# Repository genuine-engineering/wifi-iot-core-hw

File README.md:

# WIFI-IOT-CORE for IoT production project

_Wifi IoT Core_ project is to combine STM32 + ESP8266.

- ESP8266 is an amazing but cheap wifi chip. However it has many limitions, such as: no USB, limited analog interface, few I/O etc, while applications which are developed on it often need USB-Serial communication. Therefore many ESP8266-based modules in the world are added USB-TTL chip. While this brings some value to developing work, the value is just little in practical use. The design in this _Wifi IoT Core_ project uses the cheap STM32, with USB interface, to ease development, and complements many other features which are missing in ESP8266.

- The _Wifi IoT Core_ project including:

    + [wifi-iot-core-hw](https://github.com/genuine-engineering/wifi-iot-core-hw). Hardware is designed with [KiCad](http://kicad-pcb.org/)
    + [wifi-iot-core-stm32-fw](https://github.com/genuine-engineering/wifi-iot-core-stm32-fw). Firmware for STM32, based on [libopencm3](https://github.com/libopencm3/libopencm3)
    + [wifi-iot-core-esp8266-fw](https://github.com/genuine-engineering/wifi-iot-core-esp8266-fw). Firmware for ESP8266, based on [Espressif SDK 2.0](https://espressif.com/en/support/download/sdks-demos)

# Wifi-iot-core-hw
## Overview
The hardware is designed with [KiCad](http://kicad-pcb.org/) software. It includes two main components: ESP8266 and STM32F103C8T6.

 - STM32 has USB interface and is connected with ESP8266 via UART.

 - The output pins of the STM32 and ESP8266 are exposed for external use.

## Schematic

## PCB

## 3D

## BOM

| Refs                      | Value           | Footprint                            |
|---------------------------|-----------------|--------------------------------------|
| C7                        | 15pf            | lib:C_0603                           |
| C1,C9-C12,C15,C17,C19,C20 | 0.1uF           | lib:C_0603                           |
| C4,C5                     | 10pF            | lib:C_0603                           |
| C6                        | 15pF            | lib:C_0603                           |
| C16,C18                   | 1uF             | lib:C_0603                           |
| C3                        | 100nF           | lib:C_0603                           |
| C21                       | 10nF            | lib:C_0603                           |
| C2,C13,C14                | 10uF-50v        | Capacitors_SMD:C_1210                |
| C8                        | 470pF           | lib:C_0603                           |
| R11,R12                   | 22              | lib:R_0603                           |
| R10                       | 1.5K            | lib:R_0603                           |
| R2-R5                     | 10K             | lib:R_0603                           |
| R9                        | 0R              | lib:R_0603                           |
| R1,R6-R8,R13              | 10k             | lib:R_0603                           |
| SW1                       | RST             | lib:SW_SPST_B3U-1000P-B              |
| SW2                       | SW_PUSH_SMALL_H | lib:SW_SPST_B3U-1000P-B              |
| U1                        | ESP-07v2        | lib:ESP-07v2-smd-16pin               |
| U2                        | STM32F103C8Tx   | lib:LQFP-48_Pin1.7x0.3mm_Pitch0.5mm  |
| U3                        | LP2985LV        | TO_SOT_Packages_SMD:SOT-23-5         |
| P1,P2                     | CONN_01X20      | Pin_Headers:Pin_Header_Straight_1x20 |
| P7                        | CONN_01X04      | Pin_Headers:Pin_Header_Straight_1x04 |
| P3-P6                     | CONN_01X01      | lib:MountingHole_2mm                 |
| P8                        | USB             | lib:Micro_usb_B_smd                  |
| Y2                        | 32.687          | lib:crystal_smd_32.768_2Pin          |
| Y1                        | 8MHz            | lib:Crystal_SMD_5032_4Pads           |
| D2                        | Led             | LEDs:LED_0805                        |
| D1                        | Led GPIO16      | LEDs:LED_0805                        |

## Gerber file

[Wifi IOT Core HW Gerber file](assets/gerber.zip)

## CC-BY license

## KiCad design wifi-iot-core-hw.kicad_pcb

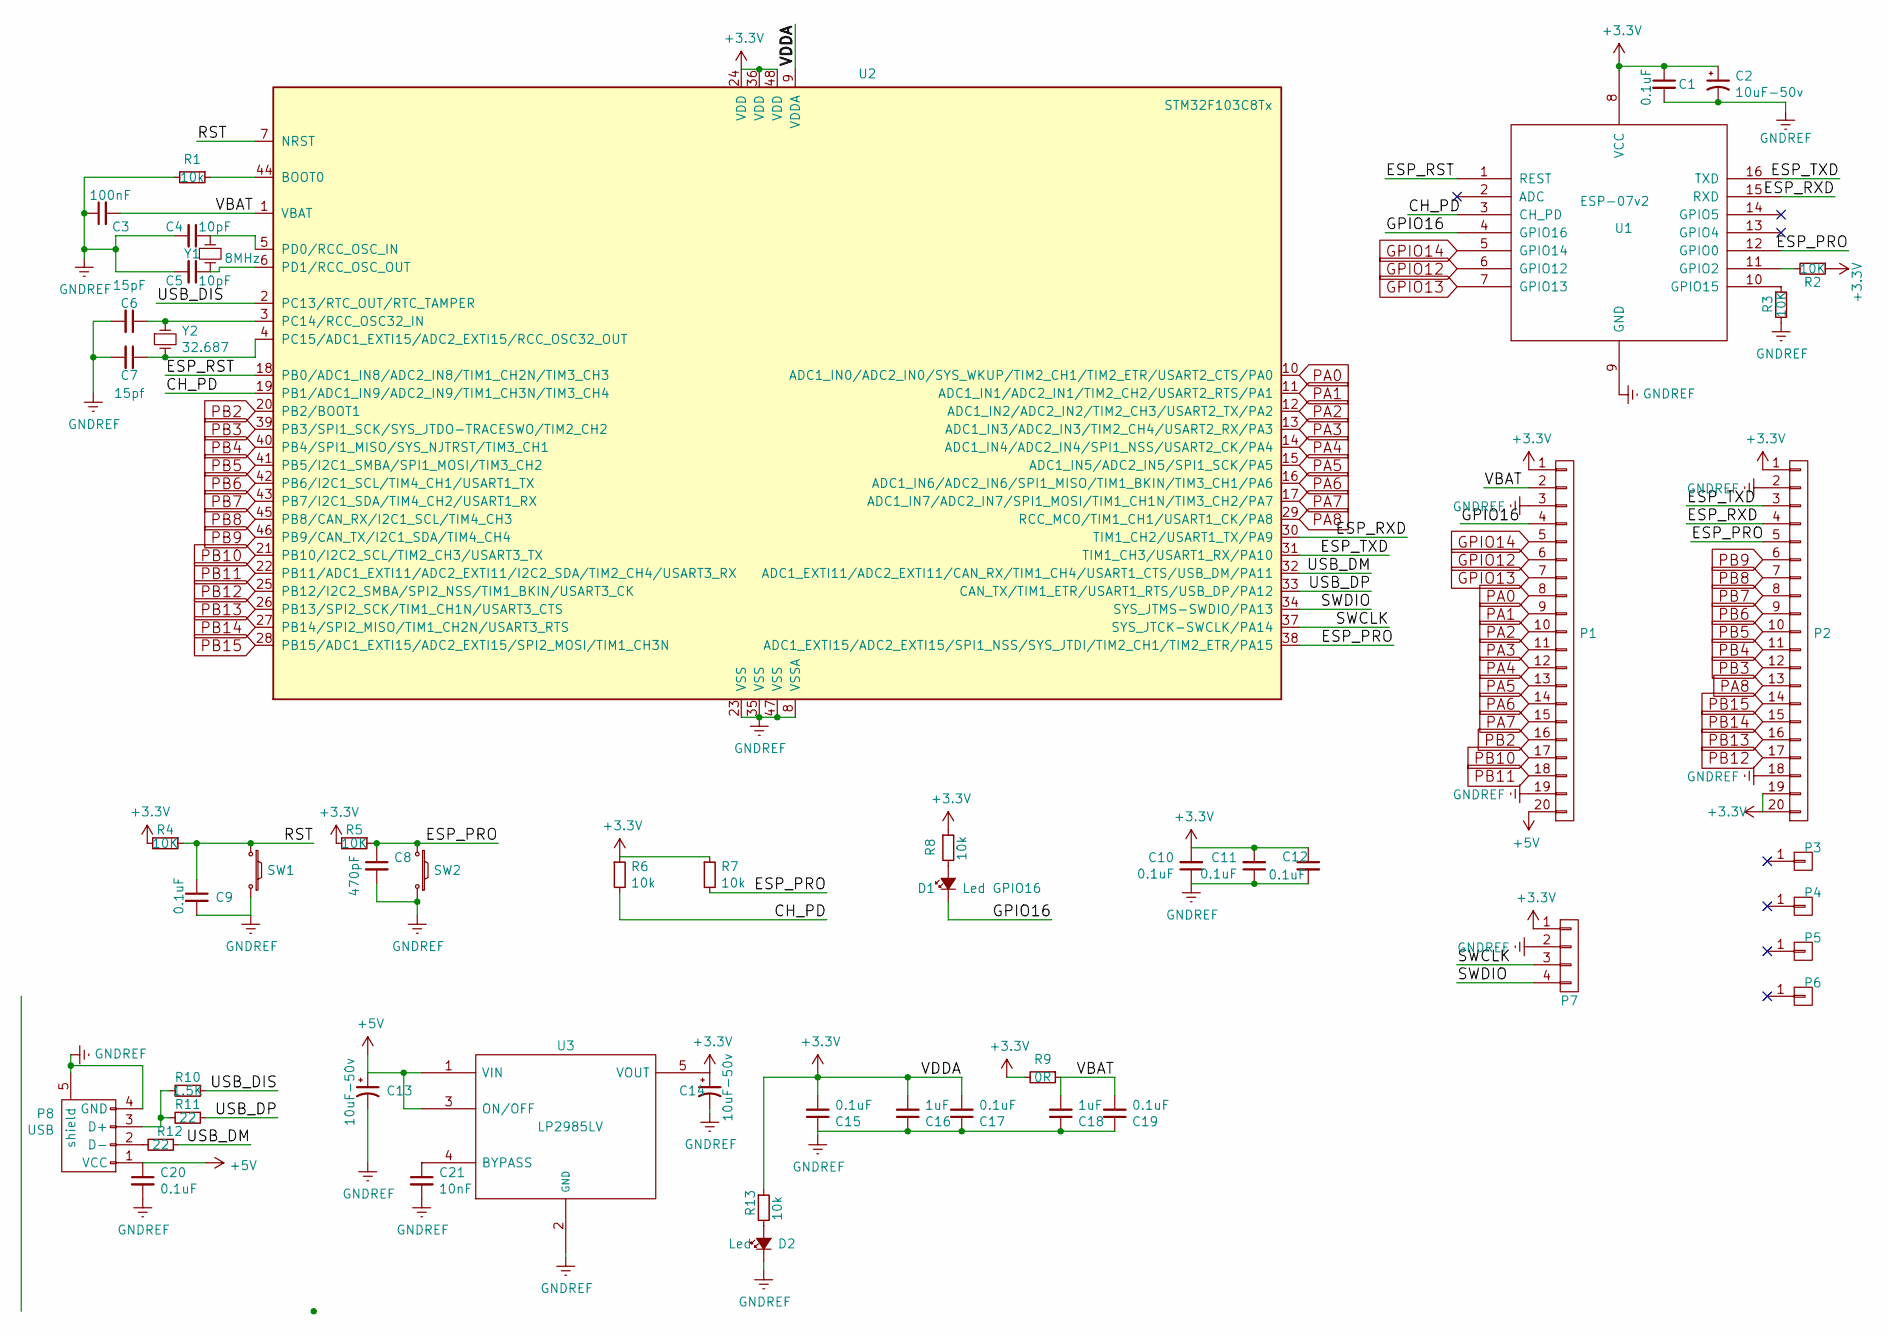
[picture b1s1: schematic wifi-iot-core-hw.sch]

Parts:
C1, C9, C10, C11, C12, C15, C17, C19, C20: 0.1uF; C_0603
C2, C13, C14: 10uF-50v; C_1210
C3: 100nF; C_0603
C4, C5: 10pF; C_0603
C6: 15pF; C_0603
C7: 15pf; C_0603
C8: 470pF; C_0603
C16, C18: 1uF; C_0603
C21: 10nF; C_0603
D1: Led GPIO16; LED_0805
D2: Led; LED_0805
P1, P2: CONN_01X20; Pin_Header_Straight_1x20
P3, P4, P5, P6: CONN_01X01; MountingHole_2mm
P7: CONN_01X04; Pin_Header_Straight_1x04
P8: USB; Micro_usb_B_smd
R1, R6, R7, R8, R13: 10k; R_0603
R2, R3, R4, R5: 10K; R_0603
R9: 0R; R_0603
R10: 1.5K; R_0603
R11, R12: 22; R_0603
SW1: RST; SW_SPST_B3U-1000P-B
SW2: SW_PUSH_SMALL_H; SW_SPST_B3U-1000P-B
U1: ESP-07v2; ESP-07v2-smd-16pin
U2: STM32F103C8Tx; LQFP-48_Pin1.7x0.3mm_Pitch0.5mm
U3: LP2985LV; SOT-23-5
Y1: 8MHz; Crystal_SMD_5032_4Pads
Y2: 32.687; crystal_smd_32.768_2Pin

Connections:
+3V3: C1.1, C2.1, C10.2, C11.2, C12.1, C14.1, C15.2, C16.2, C17.2, P1.1, P2.1, P2.19, P2.20, P7.1, R2.1, R4.2, R5.2, R6.1, R7.1, R8.1, R9.2, R13.1, U1.8 (VCC), U2.9 (VDDA), U2.24 (VDD), U2.36 (VDD), U2.48 (VDD), U3.5 (VOUT)
+5V: C13.1, C20.1, P1.20, P8.1 (VCC), U3.1 (VIN), U3.3 (ON/OFF)
/CH_PD: R6.2, U1.3 (CH_PD), U2.19 (PB1/ADC1_IN9/ADC2_IN9/TIM1_CH3N/TIM3_CH4)
/ESP_PRO: C8.1, P2.5, R5.1, R7.2, SW2.1, U1.12 (GPIO0), U2.38 (ADC1_EXTI15/ADC2_EXTI15/SPI1_NSS/SYS_JT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)
/ESP_RST: U1.1 (REST), U2.18 (PB0/ADC1_IN8/ADC2_IN8/TIM1_CH2N/TIM3_CH3)
/ESP_RXD: P2.4, U1.15 (RXD), U2.30 (TIM1_CH2/USART1_TX/PA9)
/ESP_TXD: P2.3, U1.16 (TXD), U2.31 (TIM1_CH3/USART1_RX/PA10)
/GPIO16: D1.1 (K), P1.4, U1.4 (GPIO16)
/RST: C9.1, R4.1, SW1.1, U2.7 (NRST)
/SWCLK: P7.3, U2.37 (SYS_JTCK-SWCLK/PA14)
/SWDIO: P7.4, U2.34 (SYS_JTMS-SWDIO/PA13)
/USB_DIS: R10.1, U2.2 (PC13/RTC_OUT/RTC_TAMPER)
/USB_DM: R12.1, U2.32 (ADC1_EXTI11/ADC2_EXTI11/CAN_RX/TIM1_CH4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)
/USB_DP: R11.1, U2.33 (CAN_TX/TIM1_ETR/USART1_RTS/USB_DP/PA12)
/VBAT: C3.2, C18.2, C19.2, P1.2, R9.1, U2.1 (VBAT)
GNDREF: C1.2, C2.2, C3.1, C4.2, C5.2, C6.2, C7.2, C8.2, C9.2, C10.1, C11.1, C12.2, C13.2, C14.2, C15.1, C16.1, C17.1, C18.1, C19.1, C20.2, C21.2, D2.1 (K), P1.3, P1.19, P2.2, P2.18, P7.2, P8.4 (GND), P8.5 (shield), R1.2, R3.2, SW1.2, SW2.2, U1.9 (GND), U2.8 (VSSA), U2.23 (VSS), U2.35 (VSS), U2.47 (VSS), U3.2 (GND)
GPIO12: P1.6, U1.6 (GPIO12)
GPIO13: P1.7, U1.7 (GPIO13)
GPIO14: P1.5, U1.5 (GPIO14)
unnamed: C4.1, U2.5 (PD0/RCC_OSC_IN), Y1.1
unnamed: C5.1, U2.6 (PD1/RCC_OSC_OUT), Y1.2
unnamed: C6.1, U2.3 (PC14/RCC_OSC32_IN), Y2.1
unnamed: C7.1, U2.4 (PC15/ADC1_EXTI15/ADC2_EXTI15/RCC_OSC32_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), Y2.2
unnamed: C21.1, U3.4 (BYPASS)
unnamed: D1.2 (A), R8.2
unnamed: D2.2 (A), R13.2
unnamed: P8.2 (D-), R12.2
unnamed: P8.3 (D+), R10.2, R11.2
unnamed: R1.1, U2.44 (BOOT0)
unnamed: R2.2, U1.11 (GPIO2)
unnamed: R3.1, U1.10 (GPIO15)
PA0: P1.8, U2.10 (ADC1_IN0/ADC2_IN0/SYS_WKUP/TIM2_CH1/TIM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)
PA1: P1.9, U2.11 (ADC1_IN1/ADC2_IN1/TIM2_CH2/USART2_RTS/P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)
PA2: P1.10, U2.12 (ADC1_IN2/ADC2_IN2/TIM2_CH3/USART2_TX/PA2)
PA3: P1.11, U2.13 (ADC1_IN3/ADC2_IN3/TIM2_CH4/USART2_RX/PA3)
PA4: P1.12, U2.14 (ADC1_IN4/ADC2_IN4/SPI1_NSS/USART2_CK/PA4)
PA5: P1.13, U2.15 (ADC1_IN5/ADC2_IN5/SPI1_SCK/PA5)
PA6: P1.14, U2.16 (ADC1_IN6/ADC2_IN6/SPI1_MISO/TIM1_BKIN/T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)
PA7: P1.15, U2.17 (ADC1_IN7/ADC2_IN7/SPI1_MOSI/TIM1_CH1N/T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)
PA8: P2.13, U2.29 (RCC_MCO/TIM1_CH1/USART1_CK/PA8)
PB2: P1.16, U2.20 (PB2/BOOT1)
PB3: P2.12, U2.39 (PB3/SPI1_SCK/SYS_JTDO-TRACESWO/TIM2_CH2)
PB4: P2.11, U2.40 (PB4/SPI1_MISO/SYS_NJTRST/TIM3_CH1)
PB5: P2.10, U2.41 (PB5/I2C1_SMBA/SPI1_MOSI/TIM3_CH2)
PB6: P2.9, U2.42 (PB6/I2C1_SCL/TIM4_CH1/USART1_TX)
PB7: P2.8, U2.43 (PB7/I2C1_SDA/TIM4_CH2/USART1_RX)
PB8: P2.7, U2.45 (PB8/CAN_RX/I2C1_SCL/TIM4_CH3)
PB9: P2.6, U2.46 (PB9/CAN_TX/I2C1_SDA/TIM4_CH4)
PB10: P1.17, U2.21 (PB10/I2C2_SCL/TIM2_CH3/USART3_TX)
PB11: P1.18, U2.22 (PB11/ADC1_EXTI11/ADC2_EXTI11/I2C2_SDA/T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)
PB12: P2.17, U2.25 (PB12/I2C2_SMBA/SPI2_NSS/TIM1_BKIN/USART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)
PB13: P2.16, U2.26 (PB13/SPI2_SCK/TIM1_CH1N/USART3_CTS)
PB14: P2.15, U2.27 (PB14/SPI2_MISO/TIM1_CH2N/USART3_RTS)
PB15: P2.14, U2.28 (PB15/ADC1_EXTI15/ADC2_EXTI15/SPI2_MOSI/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)

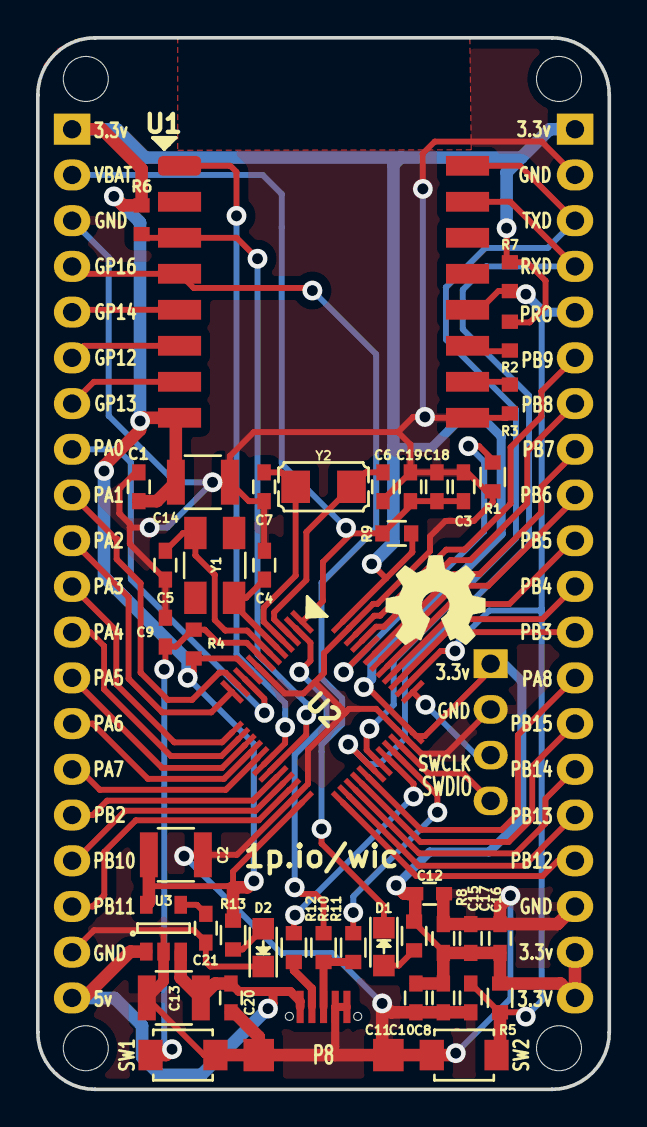
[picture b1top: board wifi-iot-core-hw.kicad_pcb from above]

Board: 2 copper layers, 31.8 x 58.4 mm, 52 parts (0 on the bottom side), 54 nets.

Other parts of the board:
VAL**: oshw_logo_500; logo5

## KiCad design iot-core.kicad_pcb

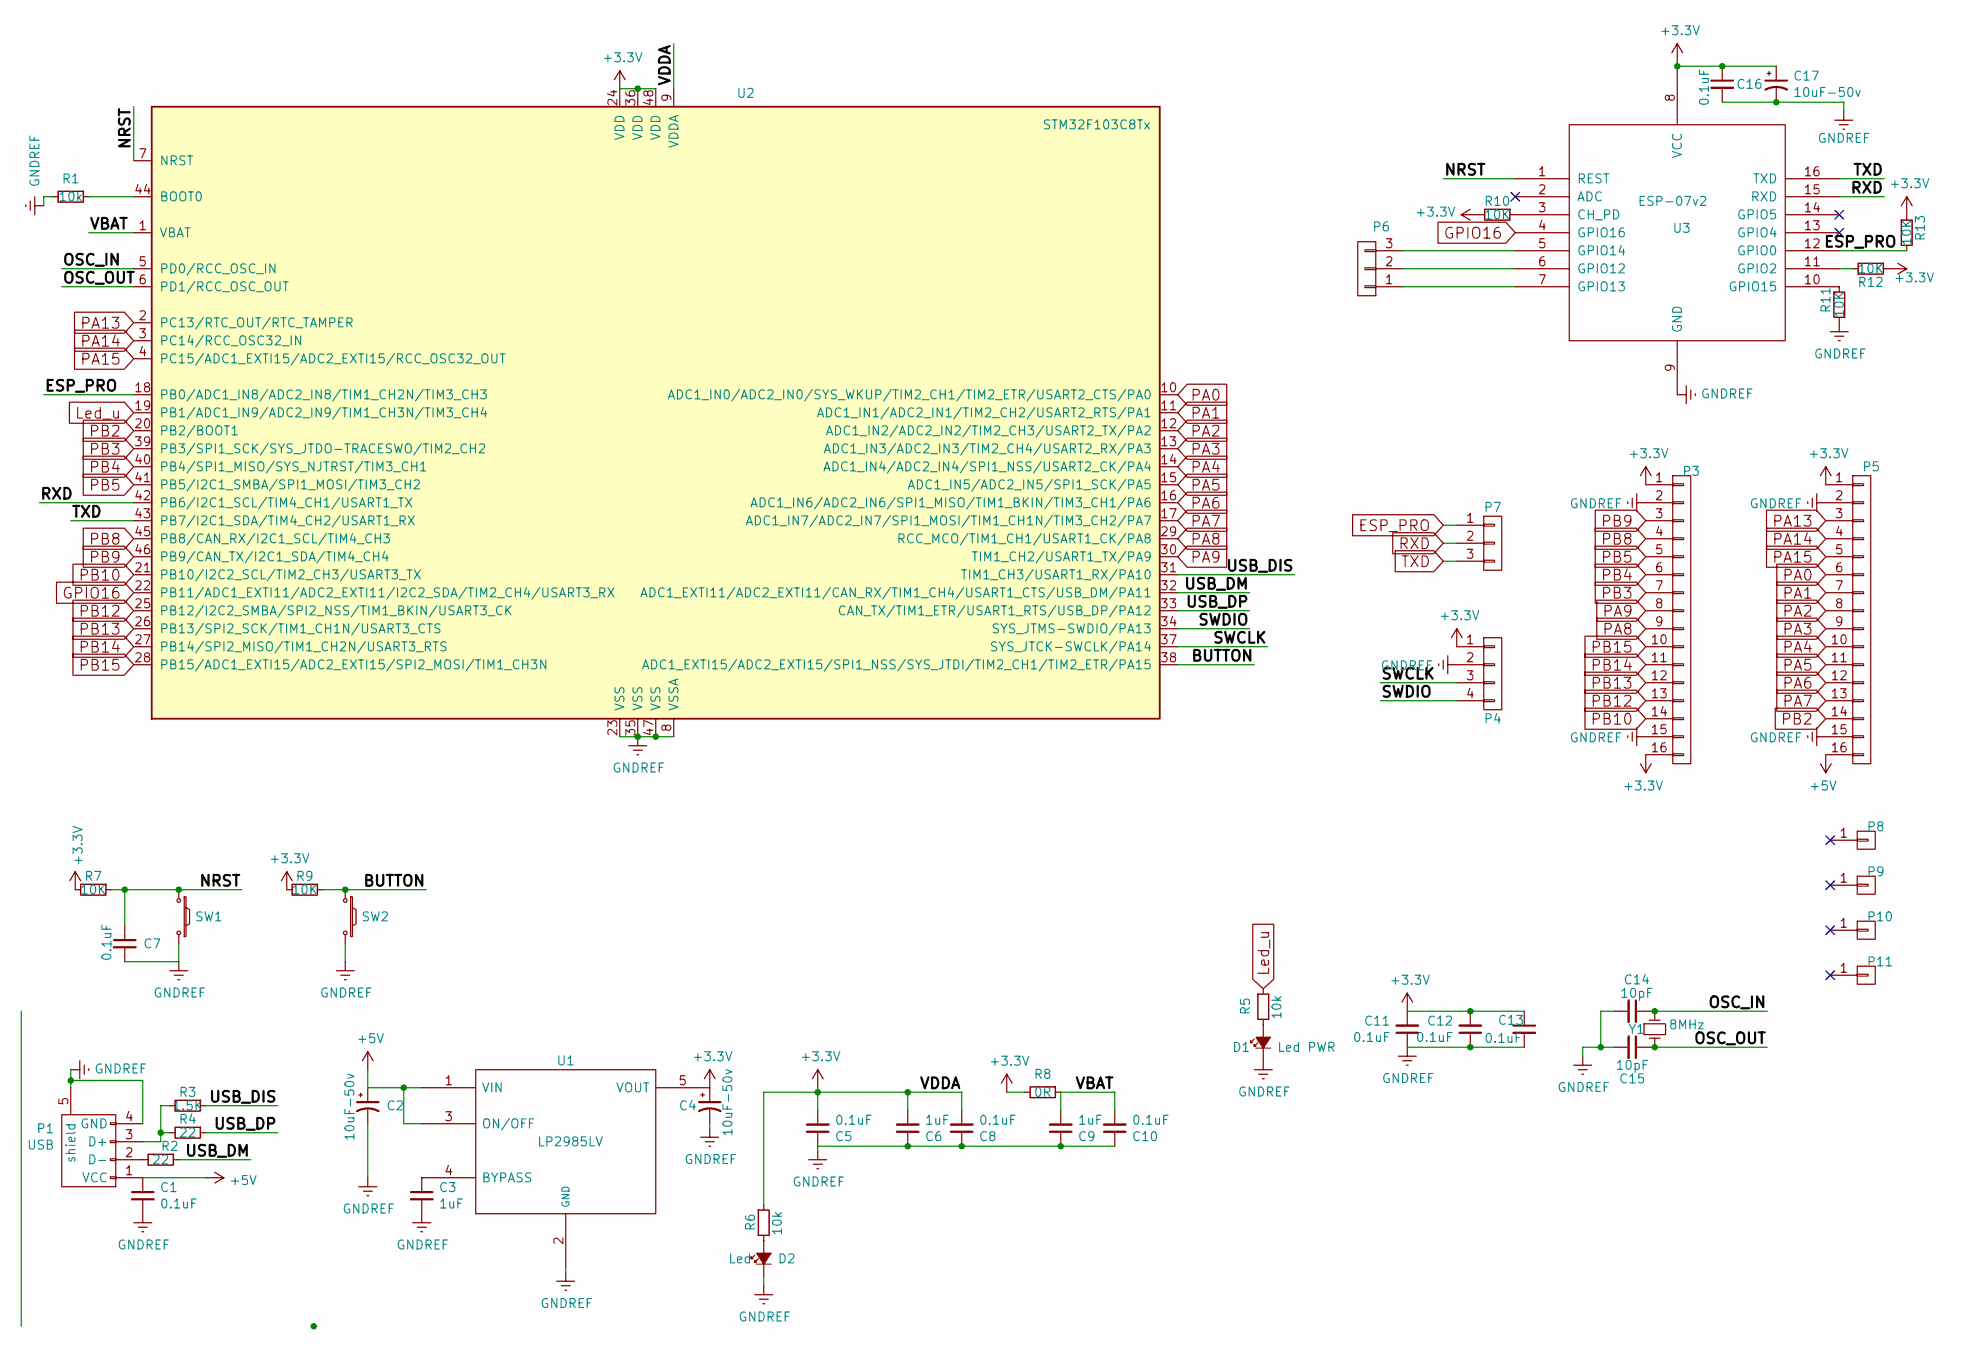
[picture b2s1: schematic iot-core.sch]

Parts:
C1, C5, C7, C8, C10, C11, C12, C13, C16: 0.1uF; C_0603
C2, C4, C17: 10uF-50v; C_1210
C3, C6, C9: 1uF; C_0603
C14, C15: 10pF; C_0603
D1: Led PWR; LED_0805
D2: Led; LED_0805
P1: USB; conn_usb_B_micro_smd-2
P3, P5: CONN_01X16; Pin_Header_Straight_1x16
P4: CONN_01X04; Pin_Header_Straight_1x04
P6, P7: CONN_01X03; Pin_Header_Straight_1x03
P8, P9, P10, P11: CONN_01X01; MountingHole_3.5mm
R1, R5, R6: 10k; R_0603
R2, R4: 22; R_0603
R3: 1.5K; R_0603
R7, R9, R10, R11, R12, R13: 10K; R_0603
R8: 0R; R_0603
SW1: RST; SW_SPST_B3U-1000P-B
SW2: SW_PUSH_SMALL_H; SW_SPST_B3U-1000P-B
U1: LP2985LV; SOT-23-5
U2: STM32F103C8Tx; LQFP-48_7x7mm_Pitch0.5mm
U3: ESP-07v2; ESP-07v2-smd-16pin
Y1: 8MHz; HC49_sm

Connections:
+3V3: C4.1, C5.2, C6.2, C8.2, C11.2, C12.2, C13.1, C16.1, C17.1, P3.1, P3.16, P4.1, P5.1, R6.1, R7.2, R8.2, R9.2, R10.2, R12.1, R13.1, U1.5 (VOUT), U2.9 (VDDA), U2.24 (VDD), U2.36 (VDD), U2.48 (VDD), U3.8 (VCC)
+5V: C1.1, C2.1, P1.1 (VCC), P5.16, U1.1 (VIN), U1.3 (ON/OFF)
/BUTTON: R9.1, SW2.1, U2.38 (ADC1_EXTI15/ADC2_EXTI15/SPI1_NSS/SYS_JT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); also elsewhere on the board
/NRST: C7.1, R7.1, SW1.1, U2.7 (NRST), U3.1 (REST); also elsewhere on the board
/OSC_IN: C14.1, U2.5 (PD0/RCC_OSC_IN), Y1.1
/OSC_OUT: C15.1, U2.6 (PD1/RCC_OSC_OUT), Y1.2
/SWCLK: P4.3, U2.37 (SYS_JTCK-SWCLK/PA14)
/SWDIO: P4.4, U2.34 (SYS_JTMS-SWDIO/PA13)
/USB_DIS: R3.1, U2.31 (TIM1_CH3/USART1_RX/PA10)
/USB_DM: R2.1, U2.32 (ADC1_EXTI11/ADC2_EXTI11/CAN_RX/TIM1_CH4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)
/USB_DP: R4.1, U2.33 (CAN_TX/TIM1_ETR/USART1_RTS/USB_DP/PA12)
/VBAT: C9.2, C10.2, R8.1, U2.1 (VBAT)
ESP_PRO: P7.1, R13.2, U2.18 (PB0/ADC1_IN8/ADC2_IN8/TIM1_CH2N/TIM3_CH3), U3.12 (GPIO0)
GNDREF: C1.2, C2.2, C3.2, C4.2, C5.1, C6.1, C7.2, C8.1, C9.1, C10.1, C11.1, C12.1, C13.2, C14.2, C15.2, C16.2, C17.2, D1.1 (K), D2.1 (K), P1.4 (GND), P1.5 (shield), P3.2, P3.15, P4.2, P5.2, P5.15, R1.2, R11.2, SW1.2, SW2.2, U1.2 (GND), U2.8 (VSSA), U2.23 (VSS), U2.35 (VSS), U2.47 (VSS), U3.9 (GND); also elsewhere on the board
GPIO16: U2.22 (PB11/ADC1_EXTI11/ADC2_EXTI11/I2C2_SDA/T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), U3.4 (GPIO16)
Led_u: R5.1, U2.19 (PB1/ADC1_IN9/ADC2_IN9/TIM1_CH3N/TIM3_CH4)
unnamed: C3.1, U1.4 (BYPASS)
unnamed: D1.2 (A), R5.2
unnamed: D2.2 (A), R6.2
unnamed: P1.2 (D-), R2.2
unnamed: P1.3 (D+), R3.2, R4.2
unnamed: P6.1, U3.7 (GPIO13)
unnamed: P6.2, U3.6 (GPIO12)
unnamed: P6.3, U3.5 (GPIO14)
unnamed: R1.1, U2.44 (BOOT0)
unnamed: R10.1, U3.3 (CH_PD)
unnamed: R11.1, U3.10 (GPIO15)
unnamed: R12.2, U3.11 (GPIO2)
PA0: P5.6, U2.10 (ADC1_IN0/ADC2_IN0/SYS_WKUP/TIM2_CH1/TIM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)
PA1: P5.7, U2.11 (ADC1_IN1/ADC2_IN1/TIM2_CH2/USART2_RTS/P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)
PA2: P5.8, U2.12 (ADC1_IN2/ADC2_IN2/TIM2_CH3/USART2_TX/PA2)
PA3: P5.9, U2.13 (ADC1_IN3/ADC2_IN3/TIM2_CH4/USART2_RX/PA3)
PA4: P5.10, U2.14 (ADC1_IN4/ADC2_IN4/SPI1_NSS/USART2_CK/PA4)
PA5: P5.11, U2.15 (ADC1_IN5/ADC2_IN5/SPI1_SCK/PA5)
PA6: P5.12, U2.16 (ADC1_IN6/ADC2_IN6/SPI1_MISO/TIM1_BKIN/T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)
PA7: P5.13, U2.17 (ADC1_IN7/ADC2_IN7/SPI1_MOSI/TIM1_CH1N/T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)
PA8: P3.9, U2.29 (RCC_MCO/TIM1_CH1/USART1_CK/PA8)
PA9: P3.8, U2.30 (TIM1_CH2/USART1_TX/PA9)
PA13: P5.3, U2.2 (PC13/RTC_OUT/RTC_TAMPER)
PA14: P5.4, U2.3 (PC14/RCC_OSC32_IN)
PA15: P5.5, U2.4 (PC15/ADC1_EXTI15/ADC2_EXTI15/RCC_OSC32_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)
PB2: P5.14, U2.20 (PB2/BOOT1)
PB3: P3.7, U2.39 (PB3/SPI1_SCK/SYS_JTDO-TRACESWO/TIM2_CH2)
PB4: P3.6, U2.40 (PB4/SPI1_MISO/SYS_NJTRST/TIM3_CH1)
PB5: P3.5, U2.41 (PB5/I2C1_SMBA/SPI1_MOSI/TIM3_CH2)
PB8: P3.4, U2.45 (PB8/CAN_RX/I2C1_SCL/TIM4_CH3)
PB9: P3.3, U2.46 (PB9/CAN_TX/I2C1_SDA/TIM4_CH4)
PB10: P3.14, U2.21 (PB10/I2C2_SCL/TIM2_CH3/USART3_TX)
PB12: P3.13, U2.25 (PB12/I2C2_SMBA/SPI2_NSS/TIM1_BKIN/USART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)
PB13: P3.12, U2.26 (PB13/SPI2_SCK/TIM1_CH1N/USART3_CTS)
PB14: P3.11, U2.27 (PB14/SPI2_MISO/TIM1_CH2N/USART3_RTS)
PB15: P3.10, U2.28 (PB15/ADC1_EXTI15/ADC2_EXTI15/SPI2_MOSI/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)
RXD: P7.2, U2.42 (PB6/I2C1_SCL/TIM4_CH1/USART1_TX), U3.15 (RXD)
TXD: P7.3, U2.43 (PB7/I2C1_SDA/TIM4_CH2/USART1_RX), U3.16 (TXD)

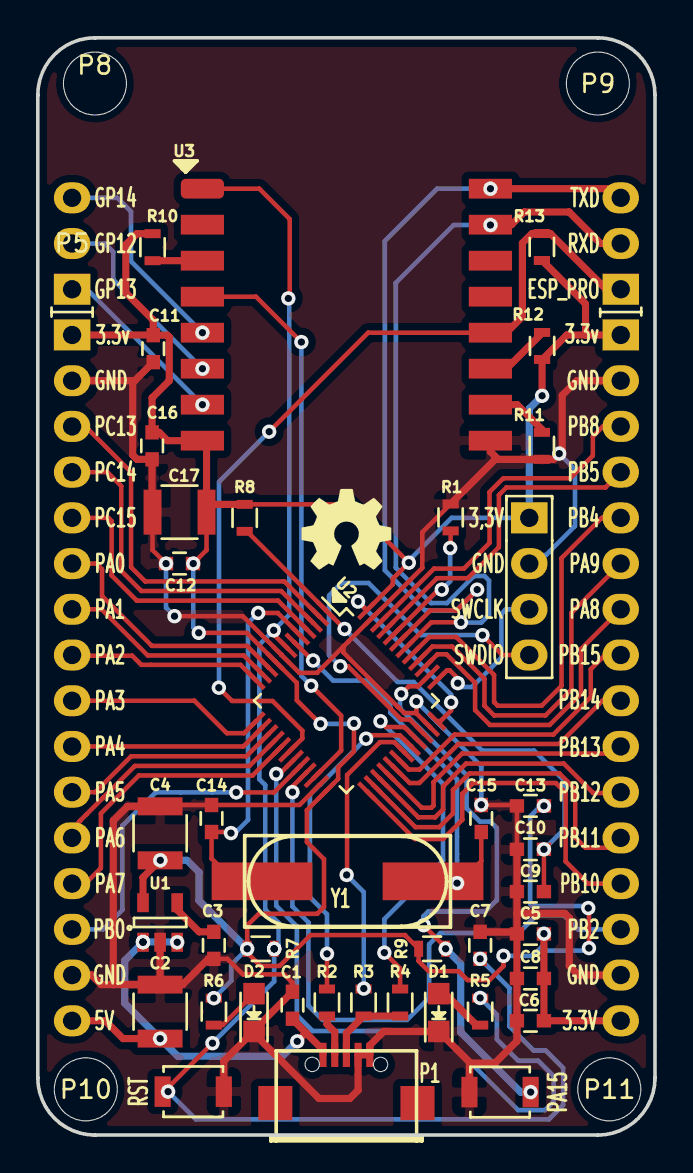
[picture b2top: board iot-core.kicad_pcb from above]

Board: 2 copper layers, 34.3 x 61.0 mm, 48 parts (0 on the bottom side), 54 nets.

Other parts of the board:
PA15: SW_PUSH_SMALL_H; SW_SPST_B3U-1000P-B
RST: RST; SW_SPST_B3U-1000P-B

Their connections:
/BUTTON: PA15.1; also elsewhere on the board
/NRST: RST.1; also elsewhere on the board
GNDREF: PA15.2, RST.2; also elsewhere on the board

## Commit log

2016-08-05 fixed format README.md
2016-08-05 add 3D image
2016-08-05 lol, mistake image tag
2016-08-05 Fix mistake
2016-08-05 Fix README
2016-08-05 Update HW
2016-08-05 Fix typo in README
2016-08-06 Confirm PIN 1 of ESP8266 & STM32
2016-08-06 Fix name headers
2016-08-08 Update README file, name pin headers, pin 1 STM32 & ESP8266
2016-08-08 ADD gerber file
2016-08-09 Modified README file, rename project, add gerber file, anh 3d. ADD lib ESP8266 & BUTTON
2016-08-09 Fix picture 3D
2016-08-09 Fix 3D online
2016-08-09 Fix link lib 3D file
2016-08-10 Fix DAO DONG THACH ANH KHONG NOI GND, pin ESP_PRO to PB0, GPIO16 to PB11,DELETE header BOOT 0
2016-08-10 Add 3D online file
2016-08-10 Add sub Englishon README file
2016-08-10 remove Vietnamese lang
2016-08-11 add bomlist
2016-08-16 Fix name project
2016-08-16 Fix my mistake save README
2016-08-17 Improve English in README
2016-08-19 Fix Schematic & PCB
2016-08-19 resolve #10
2016-08-26 Drop pin GPIO16 at pin STM32, add address support in PCB & size PCB 2,3x1,25 inch (5,8x3,2 mm)
2016-08-26 Fix assets file
